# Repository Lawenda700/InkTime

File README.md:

INKTIME

1.	Diagrama componente:

" src="https://github.com/Lawenda700/InkTime/blob/main/Images/Screenshot%20(216).png" />
)

 2.	BOM cu componentele folosite:

| Componentă | Link Producător (Datasheet & JLC) |
| :--- | :--- |
| **JUMPER_SJ** | [Link JLC](https://jlcpcb.com/partdetail/WurthElektronik-Jumper2/C2940092) |
| **C166112** | [Link JLC](https://jlcpcb.com/partdetail/RALEC-RTT017681FTH/C166112) |
| **GRM011R60J152KE01L** | [Link JLC](https://jlcpcb.com/partdetail/22429554-GRM011R60J152KE01L/C21012218) |
| **CAPACITOR_0201_L** | [Link JLC](https://jlcpcb.com/partdetail/Made_inChina-Capacitor15nf100v/C26191) |
| **CPF0201D7K68C1** | [Link JLC](https://jlcpcb.com/partdetail/TEConnectivity-CPF0201D10KC1/C4187156) |
| **CAP_0402** | [Link JLC](https://jlcpcb.com/partdetail/1879-0402B151K500NT/C1527) |
| **EVP-AKE31A_PAN** | [Link JLC](https://jlcpcb.com/partdetail/PANASONIC-EVPAKE31A/C569760) |
| **MOSFET_PCH-DMG2305UX-7** | [Link JLC](https://jlcpcb.com/parts/componentSearch?searchTxt=MOSFET_PCH-DMG2305UX-7) |
| **2450AT18B100E** | [Link JLC](https://jlcpcb.com/partdetail/JohansonDielectrics-2450AT18B100E/C2917717) |
| **INDUCTOR_0402_L** | [Link JLC](https://jlcpcb.com/partdetail/MurataElectronics-LQG15HS27NJ02D/C12669) |
| **XTAL_32KHZ** | [Link JLC](https://jlcpcb.com/partdetail/HCI-CO21H4_32_000kHz18JHPSTL/C2842) |
| **503480-2400** | [Link JLC](https://jlcpcb.com/partdetail/MOLEX-5034802400/C122434) |
| **744043680IND_4828-WE-TPC_WRE** | [Link JLC](https://jlcpcb.com/partdetail/1378-VHF160808H1N8ST/C1026) |
| **BMA423** | [Link JLC](https://jlcpcb.com/partdetail/BoschSensortec-BMA423/C189517) |
| **BQ25180YBGR** | [Link JLC](https://jlcpcb.com/partdetail/TexasInstruments-BQ25180YBGR/C3682423) |
| **DRV2605YZFR** | [Link JLC](https://jlcpcb.com/parts/componentSearch?searchTxt=DRV2605YZFR) |
| **USBLC6-2SC6Y** | [Link JLC](https://jlcpcb.com/partdetail/STMicroelectronics-USBLC62SC6Y/C2969755) |
| **MBR0530** | [Link JLC](https://jlcpcb.com/partdetail/78464-MBR0530/C77336) |
| **SI1308EDL-T1-GE3** | [Link JLC](https://jlcpcb.com/partdetail/TECHPUBLIC-SI1308EDL/C7603347) |
| **MAX17048G+T10** | [Link JLC](https://jlcpcb.com/partdetail/2777647-MAX17048GT10/C2682616) |
| **TPTP20R** | [Link JLC](https://jlcpcb.com/partdetail/DLL-PAD4Y/C24833714) |
| **KH-TYPE-C-16P** | [Link JLC](https://jlcpcb.com/partdetail/Shenzhen_KinghelmElec-KH_TYPE_C16P/C709357) |
| **MLP2016SR47MT0S1** | [Link JLC](https://jlcpcb.com/partdetail/TDK-MLP2016SR47MT0S1/C87545) |
| **NRF52840_QF** | [Link JLC](https://jlcpcb.com/partdetail/NordicSemicon-NRF52840_QFAA_FR/C3606918) |
| **RT6160AWSC** | [Link JLC](https://jlcpcb.com/partdetail/RichtekTech-RT6160AWSC/C7065276) |
| **TC2030-IDC** | [Link JLC](https://jlcpcb.com/partdetail/C90533) |
| **XTAL_37MHZ** | [Link JLC](https://jlcpcb.com/partdetail/SiTime-SIT8008AI_32_33E_37000000Y/C70717) |

3.Descriere functionalitate hardware

Produsul final( smartwatch-ul InkTime) este impartit pe mai multe module. Mai jos voi prezenta o descriere in detaliu a fiecarui modul in parte.

MCU

Microcontroller-ul nRF52840 reprezinta nucleul sistemului, acesta aflandu-se la centrul tuturor functionalitatilor oferite. Acesta este un SoC avansat optimizat pentru consum redus. Dispune astfel de un nucleu ARM Cortex-M4F cu unitate de virgulă mobilă (FPU) și suport integrat pentru BLE 5.3 (Bluetooth Low Energy). In materie de semnale de ceas acesta folosește un cristal extern de 32 MHz (HFXO) pentru procesarea rapidă și radio, respectiv un cristal de 32.768 kHz (LFXO) pentru menținerea timpului în modurile de sleep cu un consum minim de curent.

La MCU se conecteaza in primul rand un subsistem de alimentare si incarcare, pentru a mentine functionarea smartwatch-ului. Arhitectura de alimentare este concepută pentru a asigura stabilitatea tensiunii de 3.3V pe tot parcursul descărcării bateriei LiPo de 250 mAh. Modulele principale ale acestui subsistem sunt:

-LiPo Charger (BQ25180), care gestionează încărcarea și distribuția energiei prin tehnologia Power-path, permițând funcționarea sistemului în timp ce bateria se încarcă. El comunică prin I²C (adresa 0x6A) și raportează evenimente prin întreruperi pe pinul P0.11.

-Regulator DC (RT6160), ce reprezinta un convertor buck-boost care menține șina de VDD_3V3 stabilă. Acesta este configurat hardware (VSEL low) pentru a oferi o ieșire fixă și este mereu activat când sistemul este alimentat.

-Fuel Gauge (MAX17048), care monitorizează precis starea de încărcare a bateriei direct de la nodul VBAT. Utilizează interfața I²C (adresa 0x36) și poate declanșa alerte de baterie descărcată pe pinul P0.10.

- USB-C si Protecție ESD, portul USB-C fiind utilizat pentru încărcare și comunicație nativă USB cu nRF52840, iar liniile de date sunt protejate împotriva descărcărilor electrostatice prin componente dedicate montate lângă conector numite colectiv protective ESD.

Pentru ca ceasul sa ofere interactiunea cu utilizatorul caracteristica unui smartwatch, sunt introduce modulele E-Paper Drive Circuit si E-Paper Connector care se conecteaza la un E-Paper Display de 1.54 de inchi cu rezoluție de 200x200 de pixeli, optimizat pentru citirea în lumina soarelui. Acest subsistem comunică prin SPI folosind pinii: SCK (P0.02), MOSI (P0.03), CS (P0.05), DC (P0.15), RST (P0.16) și BUSY (P0.17). Pentru a elimina consumul rezidual (leakage), alimentarea ecranului (VEPD) este controlată de un tranzistor PFET (SI2301CDS). Firmware-ul activează poarta PFET (pin P1.01) doar în timpul actualizării imaginii, menținând ecranul complet deconectat electric în restul timpului. Ca si strategie de refresh se efectuează un partial refresh o dată pe minut pentru actualizarea orei și un full refresh periodic pentru a preveni efectul de "ghosting".

Pentru convenienta, putem considera urmatoarele 3 module ca facand parte dintr-un subsistem destinate interactiunii cu utilizatorul:

-Accelerometru (BMA421), care are ca functie detectarea pașilor (pedometer) și trezirea sistemului la mișcare, comunica printr-o interfață I²C (adresa 0x18) si include un algoritm integrat pentru numărarea pașilor, eliminând sarcina de procesare de pe MCU. Totodata trimite întreruperi pe pinul P0.08 (INT1) pentru trezirea sistemului.

- Haptic Driver (DRV2605L), care alerteaza utilizatorului prin vibrații discrete (ERM motor). Acesta comunică prin I²C (adresa 0x5A) pentru selectarea modelelor de vibrație. Totodata, dispune de un pin de Enable (P0.12) pentru oprirea completă a driverului între notificări.

- Butoane, 3 la numar (Up: P0.13, Down: P0.14, Enter/Esc: P1.00) conectate direct la masă (active-low). Acestea utilizează rezistențe interne de pull-up și sunt configurate ca surse de trezire din sleep.

Un ultim modul este cel de programare și depanare (SWD). Se utilizeaza interfața Tag-Connect TC2030 pentru programarea și depanarea prin SWD (Serial Wire Debug). Semnalele utilizate de catre acesta sunt: SWDIO, SWDCLK, nRESET și GND . Totodata, el este conectat la o tensiune de referinta de 3.3V pentru a permite debugger-ului să detecteze tensiunea logică a sistemului, fără a alimenta placa direct din programator.

4.	Descrierea pinilor nRF52840

   Pinii P0.06 (SDA) și P0.07 (SCL) sunt utilizati pentru magistrala I²C. Aceștia sunt configurați pentru perifericul TWI (Two-Wire Interface) al MCU-ului. Sunt utilizați pentru a comunica cu majoritatea componentelor de pe placă (accelerometru, fuel gauge, haptic driver, charger și regulator) folosind o singură pereche de fire. S-au ales acești pini pentru a centraliza controlul senzorilor și a eficientiza rutarea pe PCB.

P0.02 (SCK), P0.03 (MOSI), P0.05 (CS), P0.15 (DC - Data/Command), P0.16 (RST - Reset) si P0.17 (BUSY) sunt folositi pentru afișajul E-paper (SPI și Control). Interfața SPI este necesară pentru transferul rapid al datelor imaginii către ecran. Pinul BUSY este esențial deoarece ecranul e-paper are nevoie de timp pentru procesarea fizică a particulelor de cerneală, iar MCU-ul trebuie să aștepte semnalul de „gata” înainte de a trimite noi comenzi sau de a opri alimentarea.

P1.01 este utilizat pentru gestiunea energiei ecranului (Power Gating.). Acest pin controlează poarta tranzistorului PFET care alimentează ecranul (VEPD). Alegerea unui pin dedicat pentru power gating permite eliminarea completă a consumului de curent rezidual (leakage) al ecranului în perioadele de repaus, o strategie critică pentru atingerea autonomiei de peste 30 de zile.

P0.13 (Up), P0.14 (Down), P1.00 (Enter/Esc) sunt utilizati pentru interfața cu utilizatorul(Butoanele). Acești pini sunt utilizați cu rezistențe interne de pull-up și sunt configurați pentru a detecta tranziția la nivel „low” (apăsare). Sunt selectați special pentru capacitatea lor de a genera evenimente de trezire (wake-up) din modul Deep Sleep, permițând utilizatorului să activeze ceasul instantaneu.
P0.08 (INT1 BMA421),P1.08 (INT2 BMA421), P0.10 (ALRT MAX17048) si P0.11 (INT BQ25180) sunt utilizati ca semnale de intrerupere și trezire (Senzori). Acești pini sunt utilizați pentru a primi semnale de la senzori fără ca MCU-ul să îi interogheze constant (polling). De exemplu, pinul P0.08 permite accelerometrului să trezească ceasul doar atunci când detectează pași sau mișcare, economisind energie masiv.

P0.12 (EN) este pentru controlul haptic. Acesta permite MCU-ului să oprească alimentarea logică a driverului între notificări, prevenind orice consum inutil în perioadele de liniște.

Pentru comunicatii native si debugging avem:
- Pini dedicați USB (D+/D-): Utilizați pentru interfața nativă USB a nRF52840, necesară pentru încărcare și comunicația de date/programare.
-  SWDIO și SWDCLK: Pini dedicați pentru programare și depanare prin SWD (Serial Wire Debug), rutați către conectorul Tag-Connect pentru acces rapid la memoria flash.
- nRESET (P0.18): Pinul de reset hardware, conectat la interfața de programare pentru a permite resetarea forțată în timpul dezvoltării sau recuperării.
-ANT: Acesta este pinul de ieșire pentru semnalul radio Bluetooth. Este conectat la o rețea de adaptare a impedanței (matching network) și ulterior la antena PCB-ului. Designul trebuie să urmeze strict geometria de referință Nordic pentru a asigura performanța BLE.

-VBUS: Pin conectat la alimentarea de 5V provenită din USB pentru a permite MCU-ului să detecteze momentul în care cablul este introdus.

Pentru alimentare avem:
-VDD și VDDH: Ambii sunt conectați la șina de VDD_3V3. Deoarece tensiunea este de 3.3V, cipul funcționează în „normal-voltage mode”.
-DCC: Este pinul de ieșire al regulatorului DC/DC intern. Acesta este conectat la un circuit extern format dintr-un inductor de 10uH și unul de 15nH, care alimentează nodul DEC4/DEC6. Firmware-ul activează acest regulator (DCDC1) la runtime pentru a reduce consumul de energie.

-VSS și Exposed Pad: Sunt conectați direct la planul de masă (GND) al PCB-ului pentru a asigura o cale de întoarcere a curentului și disipare termică.

Pentru ceas, se utilizeaza 2 surse externe pentru a echilibra performanța cu economia de energie. Pinii utilizati sunt:
 XC1 și XC2: Pini pentru cristalul de 32MHz (HFXO). Acesta este ceasul de mare viteză utilizat în timpul procesării intensive și pentru funcționarea radioului BLE.
 XL1 și XL2: Pini pentru cristalul de 32.768kHz (LFXO). Acesta permite menținerea timpului (RTC) cu precizie ridicată în timp ce ceasul este în modul de somn profund (Deep Sleep).

5.	Procesul de realizare al design-ului

 S.a inceput prin realizarea schematic-ului in Fusion, conform specificatilor cerute pentru produs in fisierele MRD, PRD, ERD, Detailed Design, cat si cu ajutorul schemei de support oferite. Dupa finalizarea acestuia, rezolvarea erorilor si minimizarea warning-urilor s-a trecut la partea de pcb 2d unde s-a folosit placa specificata, iar butoanele, conectorul USB si E-Paper Display Connector au fost puse in locurile recomandate, urmand amplasarea celorlalte componente si decuparea placutei sub antenna. Apoi a inceput procesul de rutare manuala a legaturilor pe 4 layere, rutele de putere fiind realizate cu o grosime de 0.3 mm, iar celelalte rute s-au realizat cu o grosime de 0.15 mm. S-a incercat pe cat posibila evitarea vias-urilor in realizarea rutelor de putere. Din cauza aglomerarii placii s-au acceptat anumite erori de suprapunere a componentelor( cele mai multe fiind reprezentate de prinderea viasurilor in pini sau suprapuneri intre viasuri in apropierea MCU). S-au acceptat si erorile de board outline generate de modelele componentelor si cateva erori de copper clearence generate de impunerea grosimii de 0.3 mm pentru rutile de putere ce interfera cu alti pini ai anumitor componente la conectare( orice alta eroare de copper clearence a fost rezolvata). Layer-ul de ground a fost folosit exclusive pentru pinii de gnd, iar planul de masa s-a realizat pe toate cele 4 layere si s-a facut vias stitching. S-a trecut apoi la realizarea pcb-ului 3d, unde mai intai s-au important modelele 3d pentru componente, mai putin pentru test-pads pentru care s-a create de la 0 modelul 3d. Pentru adaptor modelul 3d gasit a fost redus in dimensiune pentru a incapea in carcasa. Dupa, pcb-ul a fost introdus in carcasa oferita si s-au realizat modele simpliste de baterie, display si shaker finalizand astfel etapa de proiectare.

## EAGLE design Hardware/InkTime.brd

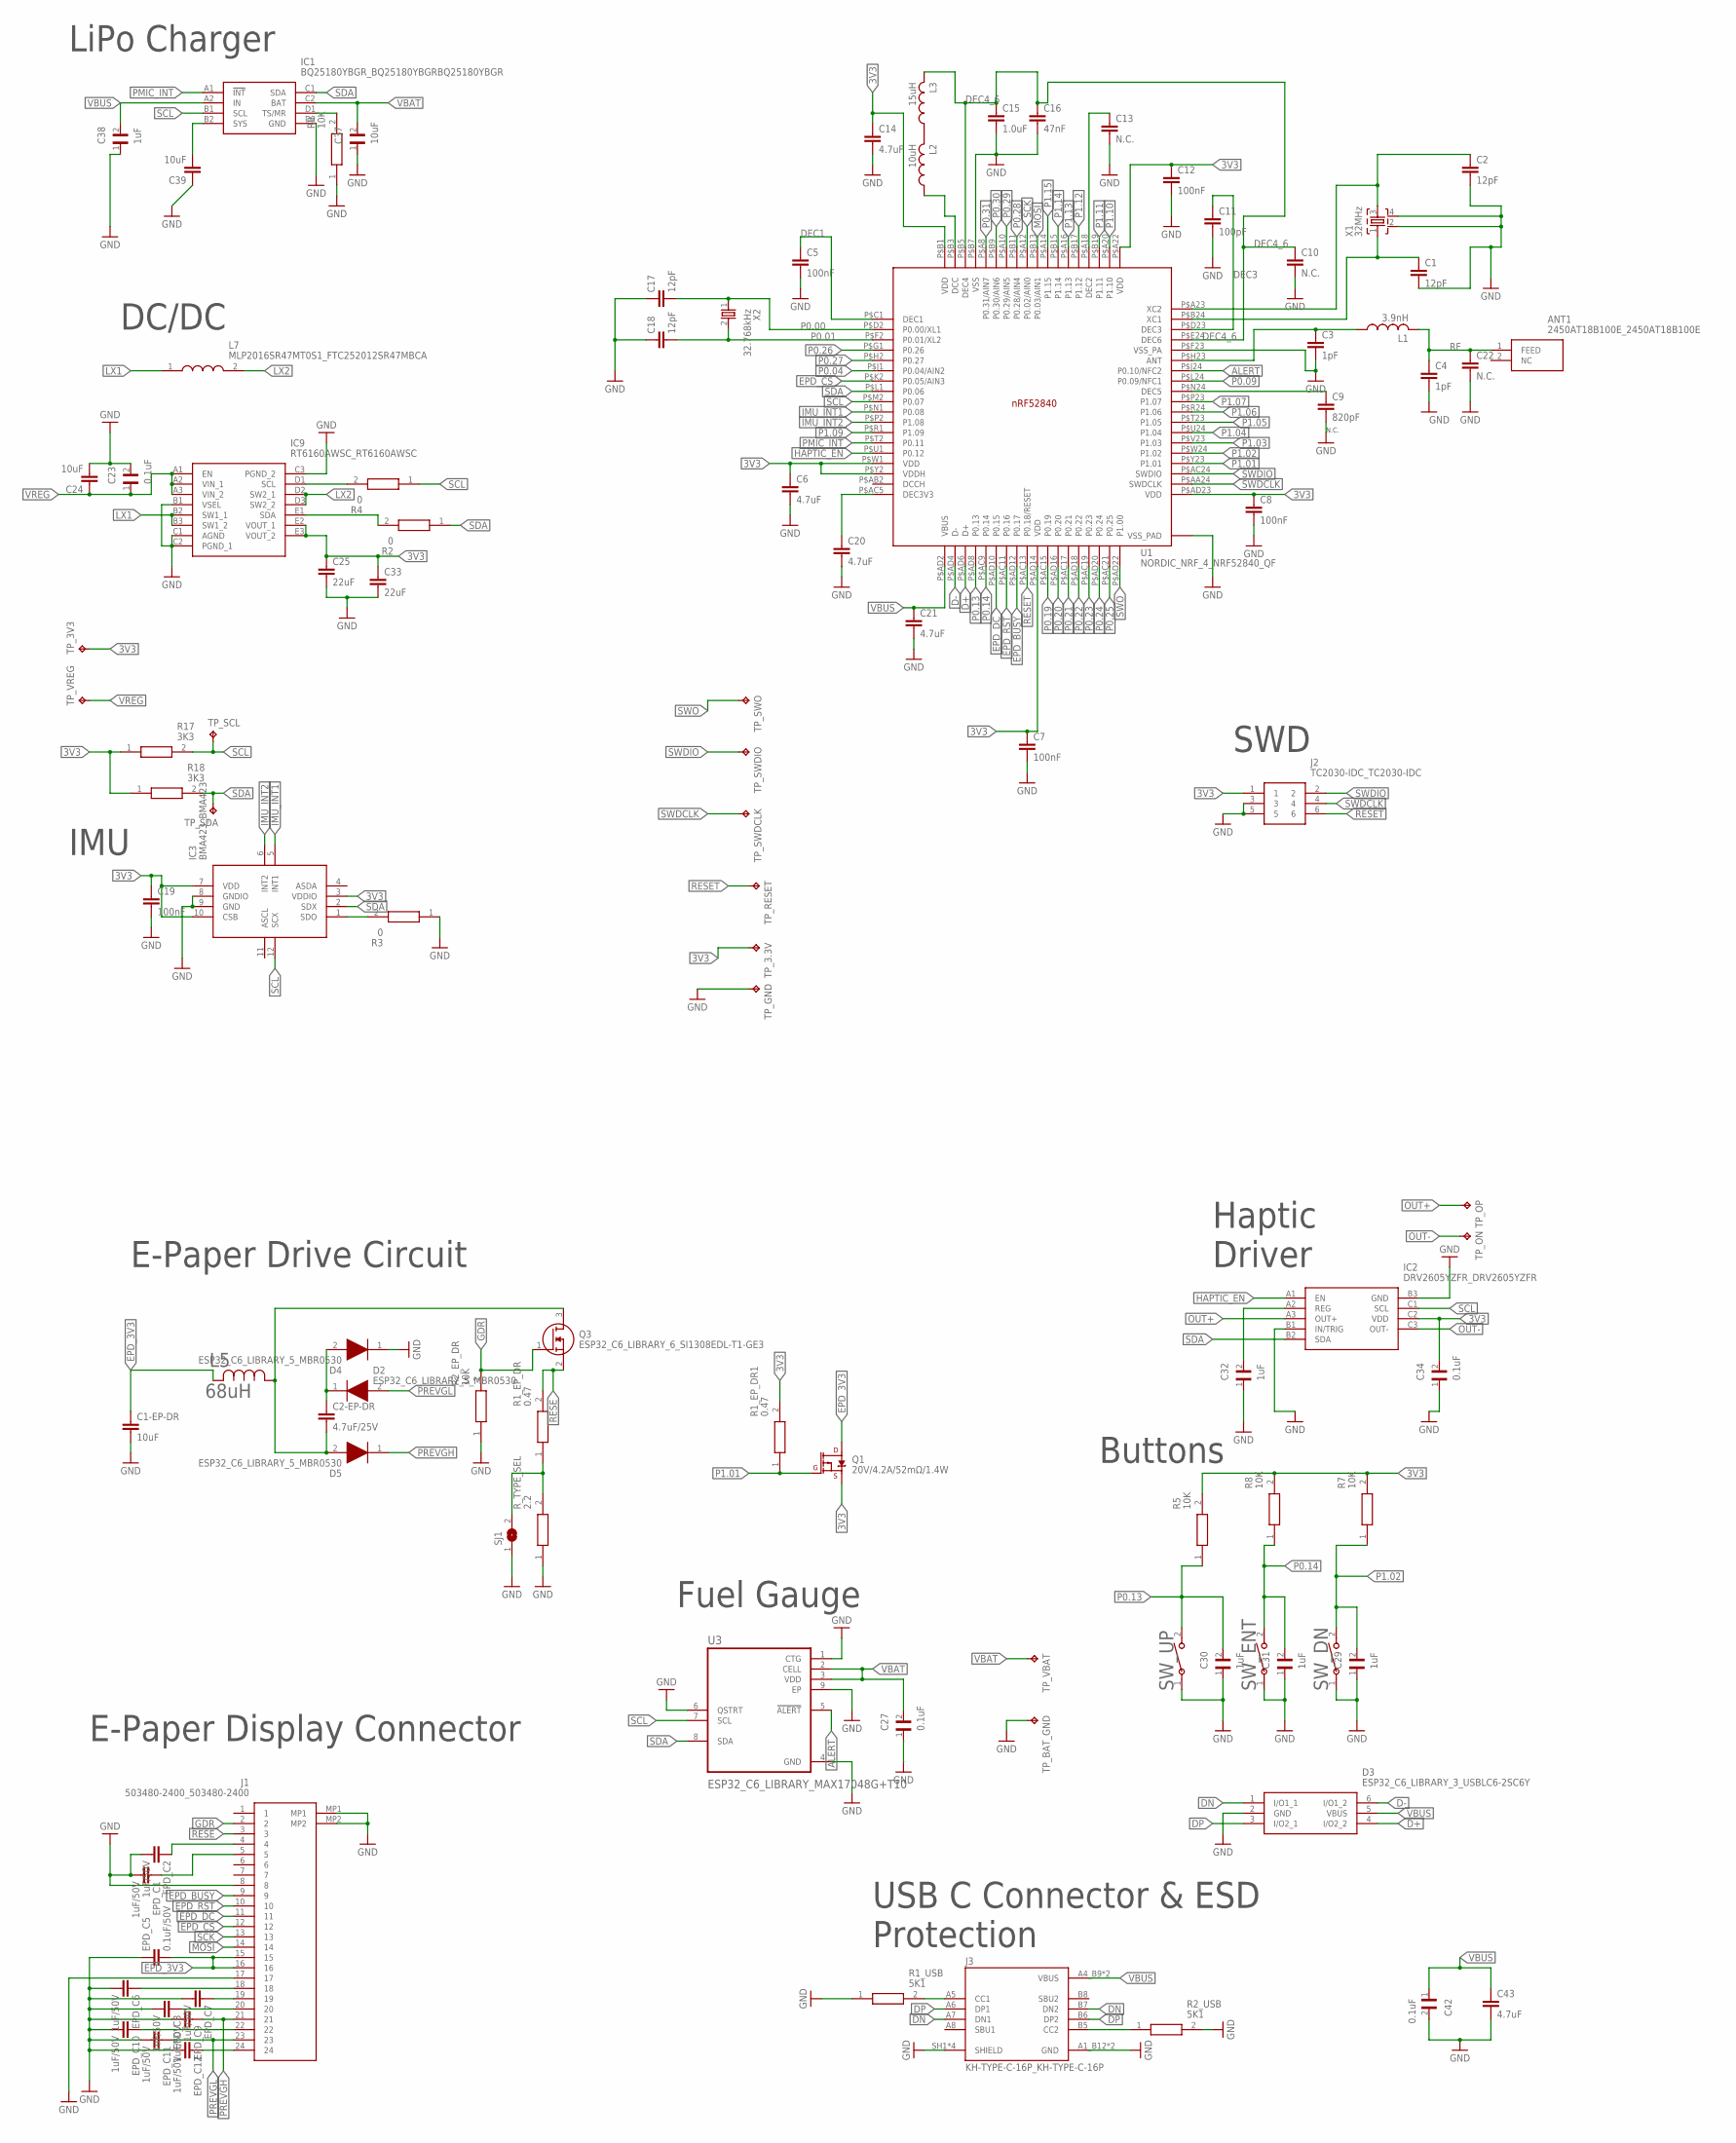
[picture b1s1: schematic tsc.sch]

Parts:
ANT1: 2450AT18B100E_2450AT18B100E; 2450AT18B100E_ANTC3216X140N
C1, C2, C17, C18: 12pF; NORDIC_NRF_3_RESC0201_L
C1-EP-DR, C24, C39: 10uF; NORDIC_NRF_3_RESC0201_L
C2-EP-DR: 4.7uF/25V; NORDIC_NRF_3_RESC0201_L
C3, C4: 1pF; NORDIC_NRF_3_RESC0201_L
C5, C7, C8, C12, C19: 100nF; NORDIC_NRF_3_RESC0201_L
C6, C14, C20, C21: 4.7uF; PERFECT_0402_0402
C9: 820pF; NORDIC_NRF_3_RESC0201_L
C10, C13, C22: N.C.; NORDIC_NRF_3_RESC0201_L
C11: 100pF; NORDIC_NRF_3_RESC0201_L
C15: 1.0uF; PERFECT_0402_0402
C16: 47nF; NORDIC_NRF_3_RESC0201_L
C23, C27, C34, C42: 0.1uF; GRM011R60J152KE01L_1_0201
C25, C33: 22uF; NORDIC_NRF_3_RESC0201_L
C29, C30, C31, C32, C38: 1uF; GRM011R60J152KE01L_1_0201
C37: 10uF; GRM011R60J152KE01L_1_0201
C43: 4.7uF; NORDIC_NRF_3_RESC0201_L
D2, D4, D5: ESP32_C6_LIBRARY_5_MBR0530; ESP32_C6_LIBRARY_5_SOD3716X135N
D3: ESP32_C6_LIBRARY_3_USBLC6-2SC6Y; ESP32_C6_LIBRARY_3_SOT95P280X145-6N
EPD_C1, EPD_C2, EPD_C6, EPD_C7, EPD_C8, EPD_C9, EPD_C10, EPD_C11, EPD_C12: 1uF/50V; NORDIC_NRF_3_RESC0201_L
EPD_C5: 0.1uF/50V; NORDIC_NRF_3_RESC0201_L
IC1: BQ25180YBGR_BQ25180YBGRBQ25180YBGR; BQ25180YBGR_BGA8C40P2X4_100X155X50
IC2: DRV2605YZFR_DRV2605YZFR; DRV2605YZFR_BGA9C50P3X3_144X144X62
IC3: BMA423_BMA423
IC9: RT6160AWSC_RT6160AWSC; RT6160AWSC_BGA15C40P3X5_140X230X60
J1: 503480-2400_503480-2400; 503480-2400_5034802400
J2: TC2030-IDC_TC2030-IDC; TC2030-IDC_TC2030IDC
J3: KH-TYPE-C-16P_KH-TYPE-C-16P; KH-TYPE-C-16P_KINGHELM_KH-TYPE-C-16P
L1: 3.9nH; NORDIC_NRF_2_RESC0402_L
L2: 10uH; NORDIC_NRF_2_RESC0402_L
L3: 15uH; NORDIC_NRF_2_RESC0402_L
L5: 68uH; ESP32_C6_LIBRARY_2_IND_4828-WE-TPC_WRE
L7: MLP2016SR47MT0S1_FTC252012SR47MBCA; MLP2016SR47MT0S1_INDC2016X100N
Q1: 20V/4.2A/52mΩ/1.4W; ESP32_C6_LIBRARY_4_ESP32_C6_LIBRARY_4_ESP32_C6_LIBRARY_4_ES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
Q3: ESP32_C6_LIBRARY_6_SI1308EDL-T1-GE3; ESP32_C6_LIBRARY_6_SOT65P210X110-3N
R1_EP_DR, R1_EP_DR1: 0.47; CPF0201D7K68C1_0201
R1_USB, R2_USB: 5K1; CPF0201D7K68C1_0201
R2, R3, R4: 0; CPF0201D7K68C1_0201
R2_EP_DR, R5, R7, R8, R9: 10K; CPF0201D7K68C1_0201
R17, R18: 3K3; CPF0201D7K68C1_0201
R_TYPE_SEL: 2.2; CPF0201D7K68C1_0201
SJ1: ESP32_C6_LIBRARY_7_JUMPER_SJ
SW_DN: 2025-10-22_07-23-44_LIBRARY_EVP-AKE31ASW_EVP-AKE3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; 2025-10-22_07-23-44_LIBRARY_SW_EVP-AKE31A_PAN
SW_ENT: 2025-10-22_07-23-44_LIBRARY_EVP-AKE31ASW_EVP-AKE3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; 2025-10-22_07-23-44_LIBRARY_SW_EVP-AKE31A_PAN
SW_UP: 2025-10-22_07-23-44_LIBRARY_EVP-AKE31ASW_EVP-AKE3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; 2025-10-22_07-23-44_LIBRARY_SW_EVP-AKE31A_PAN
TP_3.3V, TP_3V3: HECTOR_WATCH_1_TPTP20R; HECTOR_WATCH_1_TP20R
TP_BAT_GND: HECTOR_WATCH_1_TPTP20R; HECTOR_WATCH_1_TP20R
TP_GND: HECTOR_WATCH_1_TPTP20R; HECTOR_WATCH_1_TP20R
TP_ON: HECTOR_WATCH_1_TPTP20R; HECTOR_WATCH_1_TP20R
TP_OP: HECTOR_WATCH_1_TPTP20R; HECTOR_WATCH_1_TP20R
TP_RESET: HECTOR_WATCH_1_TPTP20R; HECTOR_WATCH_1_TP20R
TP_SCL: HECTOR_WATCH_1_TPTP20R; HECTOR_WATCH_1_TP20R
TP_SDA: HECTOR_WATCH_1_TPTP20R; HECTOR_WATCH_1_TP20R
TP_SWDCLK: HECTOR_WATCH_1_TPTP20R; HECTOR_WATCH_1_TP20R
TP_SWDIO: HECTOR_WATCH_1_TPTP20R; HECTOR_WATCH_1_TP20R
TP_SWO: HECTOR_WATCH_1_TPTP20R; HECTOR_WATCH_1_TP20R
TP_VBAT: HECTOR_WATCH_1_TPTP20R; HECTOR_WATCH_1_TP20R
TP_VREG: HECTOR_WATCH_1_TPTP20R; HECTOR_WATCH_1_TP20R
U1: NORDIC_NRF_4_NRF52840_QF; NORDIC_NRF_4_AQFN50P700X700X85_HS-74N
U3: ESP32_C6_LIBRARY_MAX17048G+T10; ESP32_C6_LIBRARY_SON50P200X200X80-9N
X1: 32MHz; NORDIC_NRF_BT-XTAL_2016_N
X2: 32.768kHz; NORDIC_NRF_1_XTAL_3215_N

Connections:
3V3: C6.1, C7.1, C8.1, C12.1, C14.1, C19.1, C25.1, C33.1, C34.2, IC2.C2 (VDD), IC3.3 (VDDIO), IC3.7 (VDD), IC3.10 (CSB), IC9.E2 (VOUT_1), IC9.E3 (VOUT_2), J2.1, Q1.2 (S), R1_EP_DR1.2, R5.2, R7.2, R8.2, R17.1, R18.1, TP_3.3V.TP, TP_3V3.TP, U1.P$A22 (VDD), U1.P$AD14 (VDD), U1.P$AD23 (VDD), U1.P$B1 (VDD), U1.P$W1 (VDD), U1.P$Y2 (VDDH)
ALERT: U1.P$J24 (P0.10/NFC2), U3.5 (!ALERT)
D+: D3.4 (I/O2_2), U1.P$AD6 (D+)
D-: D3.6 (I/O1_2), U1.P$AD4 (D-)
DEC1: C5.1, U1.P$C1 (DEC1)
DEC3: C11.1, C20.1, U1.P$AC5 (DEC3V3), U1.P$D23 (DEC3)
DEC4_6: C10.1, C15.1, C16.1, L3.2, U1.P$B5 (DEC4), U1.P$E24 (DEC6)
DN: D3.1 (I/O1_1), J3.A7 (DN1), J3.B7 (DN2)
DP: D3.3 (I/O2_1), J3.A6 (DP1), J3.B6 (DP2)
EPD_3V3: C1-EP-DR.1, EPD_C5.2, J1.15, J1.16, L5.2, Q1.3 (D)
EPD_BUSY: J1.9, U1.P$AD12 (P0.17)
EPD_CS: J1.12, U1.P$K2 (P0.05/AIN3)
EPD_DC: J1.11, U1.P$AD10 (P0.15)
EPD_RST: J1.10, U1.P$AC11 (P0.16)
GDR: J1.2, Q3.1 (G), R2_EP_DR.2
GND: C1.2, C1-EP-DR.2, C2.2, C3.2, C4.2, C5.2, C6.2, C7.2, C8.2, C9.2, C10.2, C11.2, C12.2, C13.2, C14.2, C15.2, C16.2, C17.1, C18.1, C19.2, C20.2, C21.2, C22.2, C23.2, C24.2, C25.2, C27.1, C29.1, C30.1, C31.1, C32.1, C33.2, C34.1, C37.1, C38.1, C39.1, C42.2, C43.2, D3.2 (GND), D4.1 (K), EPD_C1.2, EPD_C2.2, EPD_C5.1, EPD_C6.2, EPD_C7.2, EPD_C8.2, EPD_C9.2, EPD_C10.2, EPD_C11.2, EPD_C12.2, IC1.D2 (GND), IC2.B1 (IN/TRIG), IC2.B3 (GND), IC3.8 (GNDIO), IC3.9 (GND), IC9.B1 (VSEL), IC9.C1 (AGND), IC9.C2 (PGND_1), IC9.C3 (PGND_2), J1.8, J1.17, J1.MP1, J1.MP2, J2.3, J2.5, J3.A1_B12 (GND), J3.A12_B1 (GND), J3.SH1 (SHIELD), J3.SH2 (SHIELD), J3.SH3 (SHIELD), J3.SH4 (SHIELD), R1_USB.1, R2_EP_DR.1, R2_USB.2, R3.1, R9.1, R_TYPE_SEL.1, SJ1.1, SW_DN.1, SW_ENT.1, SW_UP.1, TP_BAT_GND.TP, TP_GND.TP, U1.P$74 (VSS_PAD), U1.P$75 (VSS_PAD), U1.P$76 (VSS_PAD), U1.P$77 (VSS_PAD), U1.P$78 (VSS_PAD), U1.P$79 (VSS_PAD), U1.P$80 (VSS_PAD), U1.P$81 (VSS_PAD), U1.P$82 (VSS_PAD), U1.P$83 (VSS_PAD), U1.P$84 (VSS_PAD), U1.P$85 (VSS_PAD), U1.P$86 (VSS_PAD), U1.P$87 (VSS_PAD), U1.P$88 (VSS_PAD), U1.P$89 (VSS_PAD), U1.P$90 (VSS_PAD), U1.P$B7 (VSS), U1.P$F23 (VSS_PA), U3.1 (CTG), U3.4 (GND), U3.6 (QSTRT), U3.9 (EP), X1.2, X1.4
HAPTIC_EN: IC2.A1 (EN), U1.P$U1 (P0.12)
IMU_INT1: IC3.5 (INT1), U1.P$N1 (P0.08)
IMU_INT2: IC3.6 (INT2), U1.P$P2 (P1.08)
LX1: IC9.B2 (SW1_1), IC9.B3 (SW1_2), L7.1
LX2: IC9.D2 (SW2_1), IC9.D3 (SW2_2), L7.2
MOSI: J1.14, U1.P$B13 (P0.03/AIN1)
unnamed: C9.1, U1.P$N24 (DEC5)
unnamed: C3.1, L1.1, U1.P$H23 (ANT)
unnamed: L2.2, L3.1
unnamed: C13.1, U1.P$A18 (DEC2)
unnamed: L2.1, U1.P$B3 (DCC)
unnamed: C1.1, U1.P$B24 (XC1), X1.1
unnamed: C2.1, U1.P$A23 (XC2), X1.3
unnamed: C39.2, IC1.B2 (SYS)
unnamed: IC1.D1 (TS/MR), R9.2
unnamed: IC9.D1 (SCL), R4.2
unnamed: IC9.E1 (SDA), R2.2
unnamed: IC3.1 (SDO), R3.2
unnamed: C2-EP-DR.1, D2.1 (K), D4.2 (A)
unnamed: C2-EP-DR.2, D5.2 (A), L5.1, Q3.3 (D)
unnamed: R1_EP_DR.1, R_TYPE_SEL.2, SJ1.2
unnamed: EPD_C2.1, J1.4
unnamed: EPD_C1.1, J1.5
unnamed: EPD_C6.1, J1.18
unnamed: EPD_C7.1, J1.19
unnamed: EPD_C8.1, J1.20
unnamed: J3.A5 (CC1), R1_USB.2
unnamed: EPD_C10.1, J1.22
unnamed: J3.B5 (CC2), R2_USB.1
unnamed: EPD_C12.1, J1.24
unnamed: C32.2, IC2.A2 (REG)
OUT+: IC2.A3 (OUT+), TP_OP.TP
OUT-: IC2.C3 (OUT-), TP_ON.TP
P0.00: C17.2, U1.P$D2 (P0.00/XL1), X2.1
P0.01: C18.2, U1.P$F2 (P0.01/XL2), X2.2
P0.04: U1.P$J1 (P0.04/AIN2)
P0.09: U1.P$L24 (P0.09/NFC1)
P0.13: C30.2, R5.1, SW_UP.2, U1.P$AD8 (P0.13)
P0.14: C31.2, R8.1, SW_ENT.2, U1.P$AC9 (P0.14)
P0.19: U1.P$AC15 (P0.19)
P0.20: U1.P$AD16 (P0.20)
P0.21: U1.P$AC17 (P0.21)
P0.22: U1.P$AD18 (P0.22)
P0.23: U1.P$AC19 (P0.23)
P0.24: U1.P$AD20 (P0.24)
P0.25: U1.P$AC21 (P0.25)
P0.26: U1.P$G1 (P0.26)
P0.27: U1.P$H2 (P0.27)
P0.28: U1.P$B11 (P0.28/AIN4)
P0.29: U1.P$A10 (P0.29/AIN5)
P0.30: U1.P$B9 (P0.30/AIN6)
P0.31: U1.P$A8 (P0.31/AIN7)
P1.01: Q1.1 (G), R1_EP_DR1.1, U1.P$Y23 (P1.01)
P1.02: C29.2, R7.1, SW_DN.2, U1.P$W24 (P1.02)
P1.03: U1.P$V23 (P1.03)
P1.04: U1.P$U24 (P1.04)
P1.05: U1.P$T23 (P1.05)
P1.06: U1.P$R24 (P1.06)
P1.07: U1.P$P23 (P1.07)
P1.09: U1.P$R1 (P1.09)
P1.10: U1.P$A20 (P1.10)
P1.11: U1.P$B19 (P1.11)
P1.12: U1.P$B17 (P1.12)
P1.13: U1.P$A16 (P1.13)
P1.14: U1.P$B15 (P1.14)
P1.15: U1.P$A14 (P1.15)
PMIC_INT: IC1.A1 (!INT), U1.P$T2 (P0.11)
PREVGH: D5.1 (K), EPD_C9.1, J1.21
PREVGL: D2.2 (A), EPD_C11.1, J1.23
RESE: J1.3, Q3.2 (S), R1_EP_DR.2
RESET: J2.6, TP_RESET.TP, U1.P$AC13 (P0.18/RESET)
RF: ANT1.1 (FEED), C4.1, C22.1, L1.2
SCK: J1.13, U1.P$A12 (P0.02/AIN0)
SCL: IC1.B1 (SCL), IC2.C1 (SCL), IC3.12 (SCX), R4.1, R17.2, TP_SCL.TP, U1.P$M2 (P0.07), U3.7 (SCL)
SDA: IC1.C1 (SDA), IC2.B2 (SDA), IC3.2 (SDX), R2.1, R18.2, TP_SDA.TP, U1.P$L1 (P0.06), U3.8 (SDA)
SWDCLK: J2.4, TP_SWDCLK.TP, U1.P$AA24 (SWDCLK)
SWDIO: J2.2, TP_SWDIO.TP, U1.P$AC24 (SWDIO)
SWO: TP_SWO.TP, U1.P$AD22 (P1.00)
VBAT: C27.2, C37.2, IC1.C2 (BAT), TP_VBAT.TP, U3.2 (CELL), U3.3 (VDD)
VBUS: C21.1, C38.2, C42.1, C43.1, D3.5 (VBUS), IC1.A2 (IN), J3.A4_B9 (VBUS), J3.A9_B4 (VBUS), U1.P$AD2 (VBUS)
VREG: C23.1, C24.1, IC9.A1 (EN), IC9.A2 (VIN_1), IC9.A3 (VIN_2), TP_VREG.TP

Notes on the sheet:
LiPo Charger
N.C.
DC/DC
IMU
SWD
E-Paper Drive Circuit
E-Paper Display Connector
Fuel Gauge
USB C Connector & ESD Protection
Buttons
Haptic Driver

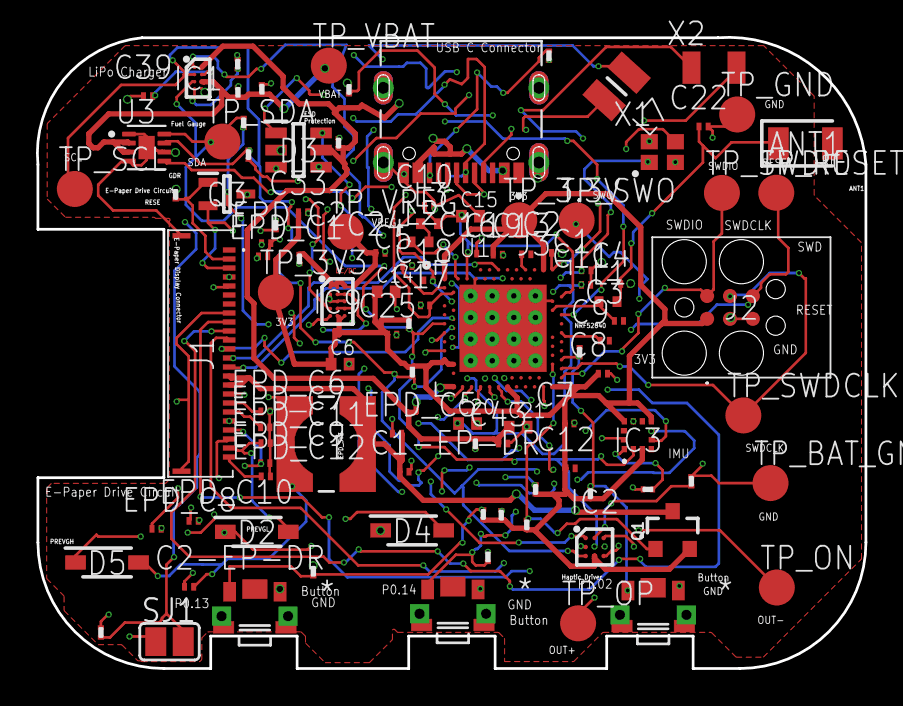
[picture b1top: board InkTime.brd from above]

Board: 2 copper layers, 46.0 x 35.1 mm, 105 parts (0 on the bottom side), 70 nets.

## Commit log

2026-04-10 Proiect faza 1
2026-04-10 Am pus poza cu diagrama pentru Readme
2026-04-10 Update README.md 2
2026-04-10 Update README.md 3
2026-04-17 Am rezolvat issue-urile din review

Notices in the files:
parts and their libraries:
COPYRIGHT: Copyright (C) 2024 Ultra Librarian. All rights reserved.
COPYRIGHT: Copyright (C) 2025 Ultra Librarian. All rights reserved.
